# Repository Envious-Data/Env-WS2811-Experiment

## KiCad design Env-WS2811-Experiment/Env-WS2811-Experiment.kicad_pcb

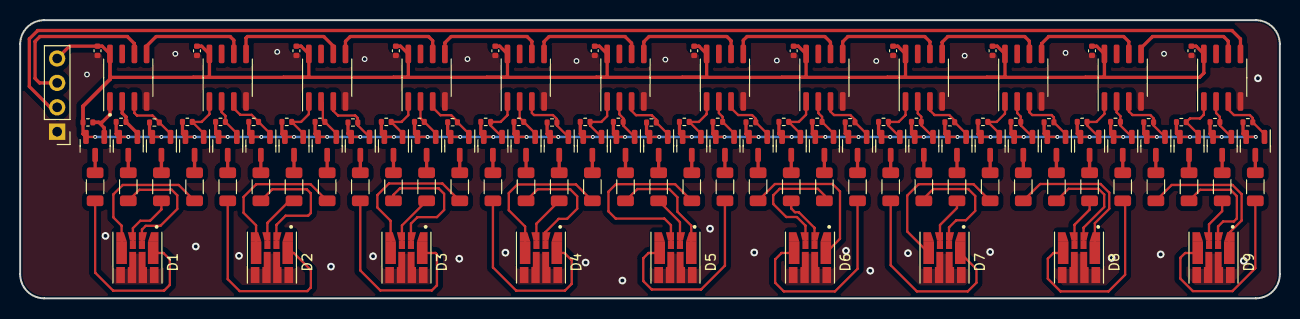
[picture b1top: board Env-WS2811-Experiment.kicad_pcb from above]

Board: 2 copper layers, 131.1 x 29.0 mm, 142 parts (0 on the bottom side), 123 nets.

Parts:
C1, C2, C3, C4, C5, C6, C7, C8, C9, C10, C11, C12: 0402 100uF; C_0402_1005Metric
D1, D2, D3, D4, D5, D6, D7, D8, D9: GW J9LHS2.4M-C0C7-2+35+13+57AW-1; LED_CLQ6A-TKW-C1L1R1H1QBB7935CC3
J1: Conn_01x04; PinHeader_1x04_P2.54mm_Vertical
Q1, Q2, Q3, Q4, Q5, Q6, Q7, Q8, Q9, Q10, Q11, Q12, Q13, Q14, Q15, Q16, Q17, Q18, Q19, Q20, Q21, Q22, Q23, Q24, Q25, Q26, Q27, Q28, Q29, Q30, Q31, Q32, Q33, Q34, Q35, Q36: Si2301DS; SOT-23
R1, R2, R3, R8, R10, R12, R14, R16, R18, R20, R22, R24, R26, R28, R31, R32, R34, R37, R38, R40, R43, R44, R46, R48, R50, R52, R55, R56, R58, R61, R62, R64, R67, R68, R70, R72: 10K 0402; R_0402_1005Metric
R4, R5, R6, R7, R9, R11, R13, R15, R17, R19, R21, R23, R25, R27, R29, R30, R33, R35, R36, R39, R41, R42, R45, R47, R49, R51, R53, R54, R57, R59, R60, R63, R65, R66, R69, R71: 20r 1206; R_1206_3216Metric
U1, U2, U3, U4, U5, U6, U7, U8, U9, U10, U11, U12: WS2811; SOIC-8_3.9x4.9mm_P1.27mm

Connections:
+5V: C1.1, C2.1, C3.1, C4.1, C5.1, C6.1, C7.1, C8.1, C9.1, C10.1, C11.1, C12.1, J1.4, Q1.2 (S), Q2.2 (S), Q3.2 (S), Q4.2 (S), Q5.2 (S), Q6.2 (S), Q7.2 (S), Q8.2 (S), Q9.2 (S), Q10.2 (S), Q11.2 (S), Q12.2 (S), Q13.2 (S), Q14.2 (S), Q15.2 (S), Q16.2 (S), Q17.2 (S), Q18.2 (S), Q19.2 (S), Q20.2 (S), Q21.2 (S), Q22.2 (S), Q23.2 (S), Q24.2 (S), Q25.2 (S), Q26.2 (S), Q27.2 (S), Q28.2 (S), Q29.2 (S), Q30.2 (S), Q31.2 (S), Q32.2 (S), Q33.2 (S), Q34.2 (S), Q35.2 (S), Q36.2 (S), R1.1, R2.1, R3.2, R8.1, R10.1, R12.2, R14.1, R16.1, R18.2, R20.1, R22.1, R24.2, R26.1, R28.1, R31.2, R32.1, R34.1, R37.1, R38.2, R40.1, R43.1, R44.2, R46.1, R48.2, R50.1, R52.1, R55.2, R56.1, R58.1, R61.1, R62.2, R64.1, R67.1, R68.2, R70.1, R72.2, U1.8 (VDD), U2.8 (VDD), U3.8 (VDD), U4.8 (VDD), U5.8 (VDD), U6.8 (VDD), U7.8 (VDD), U8.8 (VDD), U9.8 (VDD), U10.8 (VDD), U11.8 (VDD), U12.8 (VDD)
DIN: J1.3, U1.6 (DIN)
DOUT: J1.2, U12.5 (DO)
GND: C1.2, C2.2, C3.2, C4.2, C5.2, C6.2, C7.2, C8.2, C9.2, C10.2, C11.2, C12.2, D1.5, D1.6, D1.6_1, D1.7, D1.7_1, D1.8, D2.5, D2.6, D2.6_1, D2.7, D2.7_1, D2.8, D3.5, D3.6, D3.6_1, D3.7, D3.7_1, D3.8, D4.5, D4.6, D4.6_1, D4.7, D4.7_1, D4.8, D5.5, D5.6, D5.6_1, D5.7, D5.7_1, D5.8, D6.5, D6.6, D6.6_1, D6.7, D6.7_1, D6.8, D7.5, D7.6, D7.6_1, D7.7, D7.7_1, D7.8, D8.5, D8.6, D8.6_1, D8.7, D8.7_1, D8.8, D9.5, D9.6, D9.6_1, D9.7, D9.7_1, D9.8, J1.1, U1.4 (GND), U2.4 (GND), U3.4 (GND), U4.4 (GND), U5.4 (GND), U6.4 (GND), U7.4 (GND), U8.4 (GND), U9.4 (GND), U10.4 (GND), U11.4 (GND), U12.4 (GND)
unnamed: D1.1, R6.2
unnamed: D1.2, R5.2
unnamed: D1.3, R4.2
unnamed: D1.4, R7.2
unnamed: D2.1, R9.2
unnamed: D2.2, R11.2
unnamed: D2.3, R13.2
unnamed: D2.4, R15.2
unnamed: D3.1, R17.2
unnamed: D3.2, R19.2
unnamed: D3.3, R21.2
unnamed: D3.4, R23.2
unnamed: D4.1, R25.2
unnamed: D4.2, R27.2
unnamed: D4.3, R29.2
unnamed: D4.4, R30.2
unnamed: D5.1, R33.2
unnamed: D5.2, R36.2
unnamed: D5.3, R35.2
unnamed: D5.4, R39.2
unnamed: D6.1, R42.2
unnamed: D6.2, R41.2
unnamed: D6.3, R45.2
unnamed: D6.4, R47.2
unnamed: D7.1, R49.2
unnamed: D7.2, R51.2
unnamed: D7.3, R53.2
unnamed: D7.4, R54.2
unnamed: D8.1, R57.2
unnamed: D8.2, R60.2
unnamed: D8.3, R59.2
unnamed: D8.4, R63.2
unnamed: D9.1, R66.2
unnamed: D9.2, R65.2
unnamed: D9.3, R69.2
unnamed: D9.4, R71.2
unnamed: Q1.3 (D), R6.1
unnamed: Q1.1 (G), R1.2, U1.1 (OUTR)
unnamed: Q2.3 (D), R5.1
unnamed: Q2.1 (G), R2.2, U1.2 (OUTG)
unnamed: Q3.3 (D), R4.1
unnamed: Q3.1 (G), R3.1, U1.3 (OUTB)
unnamed: Q4.3 (D), R7.1
unnamed: Q4.1 (G), R8.2, U2.1 (OUTR)
unnamed: Q5.3 (D), R9.1
unnamed: Q5.1 (G), R10.2, U2.2 (OUTG)
unnamed: Q6.3 (D), R11.1
unnamed: Q6.1 (G), R12.1, U2.3 (OUTB)
unnamed: Q7.3 (D), R13.1
unnamed: Q7.1 (G), R14.2, U3.1 (OUTR)
unnamed: Q8.3 (D), R15.1
unnamed: Q8.1 (G), R16.2, U3.2 (OUTG)
unnamed: Q9.3 (D), R17.1
unnamed: Q9.1 (G), R18.1, U3.3 (OUTB)
unnamed: Q10.3 (D), R19.1
unnamed: Q10.1 (G), R20.2, U4.1 (OUTR)
unnamed: Q11.3 (D), R21.1
unnamed: Q11.1 (G), R22.2, U4.2 (OUTG)
unnamed: Q12.3 (D), R23.1
unnamed: Q12.1 (G), R24.1, U4.3 (OUTB)
unnamed: Q13.3 (D), R25.1
unnamed: Q13.1 (G), R26.2, U5.1 (OUTR)
unnamed: Q14.3 (D), R27.1
unnamed: Q14.1 (G), R28.2, U5.2 (OUTG)
unnamed: Q15.3 (D), R29.1
unnamed: Q15.1 (G), R31.1, U5.3 (OUTB)
unnamed: Q16.3 (D), R30.1
unnamed: Q16.1 (G), R32.2, U6.1 (OUTR)
unnamed: Q17.3 (D), R33.1
unnamed: Q17.1 (G), R34.2, U6.2 (OUTG)
unnamed: Q18.3 (D), R35.1
unnamed: Q18.1 (G), R37.2, U7.1 (OUTR)
unnamed: Q19.3 (D), R36.1
unnamed: Q19.1 (G), R38.1, U6.3 (OUTB)
unnamed: Q20.3 (D), R39.1
unnamed: Q20.1 (G), R40.2, U7.2 (OUTG)
unnamed: Q21.3 (D), R41.1
unnamed: Q21.1 (G), R43.2, U8.1 (OUTR)
unnamed: Q22.3 (D), R42.1
unnamed: Q22.1 (G), R44.1, U7.3 (OUTB)
unnamed: Q23.3 (D), R45.1
unnamed: Q23.1 (G), R46.2, U8.2 (OUTG)
unnamed: Q24.3 (D), R47.1
unnamed: Q24.1 (G), R48.1, U8.3 (OUTB)
unnamed: Q25.3 (D), R49.1
unnamed: Q25.1 (G), R50.2, U9.1 (OUTR)
unnamed: Q26.3 (D), R51.1
unnamed: Q26.1 (G), R52.2, U9.2 (OUTG)
unnamed: Q27.3 (D), R53.1
unnamed: Q27.1 (G), R55.1, U9.3 (OUTB)
unnamed: Q28.3 (D), R54.1
unnamed: Q28.1 (G), R56.2, U10.1 (OUTR)
unnamed: Q29.3 (D), R57.1
unnamed: Q29.1 (G), R58.2, U10.2 (OUTG)
unnamed: Q30.3 (D), R59.1
unnamed: Q30.1 (G), R61.2, U11.1 (OUTR)
unnamed: Q31.3 (D), R60.1
unnamed: Q31.1 (G), R62.1, U10.3 (OUTB)
unnamed: Q32.3 (D), R63.1
unnamed: Q32.1 (G), R64.2, U11.2 (OUTG)
unnamed: Q33.3 (D), R65.1
unnamed: Q33.1 (G), R67.2, U12.1 (OUTR)
unnamed: Q34.3 (D), R66.1
unnamed: Q34.1 (G), R68.1, U11.3 (OUTB)
unnamed: Q35.3 (D), R69.1
unnamed: Q35.1 (G), R70.2, U12.2 (OUTG)
unnamed: Q36.3 (D), R71.1
unnamed: Q36.1 (G), R72.1, U12.3 (OUTB)
unnamed: U1.5 (DO), U2.6 (DIN)
unnamed: U2.5 (DO), U3.6 (DIN)
unnamed: U3.5 (DO), U4.6 (DIN)
unnamed: U4.5 (DO), U5.6 (DIN)
unnamed: U5.5 (DO), U6.6 (DIN)
unnamed: U6.5 (DO), U7.6 (DIN)
unnamed: U7.5 (DO), U8.6 (DIN)
unnamed: U8.5 (DO), U9.6 (DIN)
unnamed: U9.5 (DO), U10.6 (DIN)
unnamed: U10.5 (DO), U11.6 (DIN)
unnamed: U11.5 (DO), U12.6 (DIN)

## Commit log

2023-07-05 initial commit +1
2023-07-05 moved kicad files to subfolder
2023-07-05 swap some mosfets over to more compact versions
